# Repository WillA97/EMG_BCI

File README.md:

# EMG_BCI

## Introduction
This repository contains the documentation, hardware files, and software files for a simple electromyogram front end. The purpose is to create a simple interface to aquire the signals and also improve my hardware and software design skills. It's mostly for fun

## High level requirements

- Amplifier the signals from a 2 electrode from an EMG signal
- transfer the data from to a secondary device

## Hardware block diagram

```mermaid
graph TD
    A[EMG Electrodes<br>500 µV - 1 mV] --> B[Instrumentation Amplifier<br>Gain: 50<br>High Z, High CMRR]
    B --> C[High-Pass Filter<br>Cutoff: 10 Hz]
    C --> D[Gain Stage<br>Gain: 20<br>Total Gain: 1000]
    D --> E[Low-Pass Filter<br>Cutoff: 500 Hz]
    E --> F[Rectifier]
    E --> G[Offset Stage<br>Shift to 1.5V]
    G --> H[ADC 1<br>Un-rectified]
    F --> I[ADC 2<br>Rectified]

```
- The EMG signals will be around 500 uV - 1 mV. Will scale the signals with a gain of about 1000 to make the output swing around 0.5 - 1 V
- The first stage is the instrumentation amplifier. It has a very high impedence input, and large common mode rejection. It also has a gain stage built in, which is chosen as 50
- The second stage would be the high pass filter. Removed any high frequency signals and prevents aliasing when sampling occurs. The cutoff frequency is 10 Hz, which is the lower frequency of the muscle fibers
- The third stage is a gain stage. The gain is set to 20, putting the final gain at 1000.
- The fourth state is the low pass filter. The cutoff frequency was set to 500 Hz, which is the upper limit of the muscle fibers.
- The fifth stage is the rectifier stage.
- The sixth stage is the offset stage, which adds an offset to shift the 0 point of the signal to be 1.5V. This is because many microcontrollers use +3.3V and we want to avoid applying a negative voltage on the ADC
- The sevent stage is the ADC, which can record the EMG signals. To give some options about which signal can be used in the signal processing. I want to use one ADC for the un-rectified signal, and another for the rectified signal.

- There are a couple of options when using the signal for an EMG:
  
  - one option is to use the raw EMG data and do the signal processing on those values. After performing an FFT will get the frequency data from them
  - another option is to rectify the signal, this would give an positive average value for the signal
  - with the rectified signal, can take the RMS and filterd values of it to get the average value of the amount of exertion from the muscles
 
## Communication interface

- The communication interface will be used to transfer the digitized EMG signals to an external device. The ADC chosen (MCP 3202) uses an SPI interface.

## Test results 
Here are some of the results from testing the front end. The analog discovery module was used to insert a signal at the front of the instrumentation amplifier and the output at the different test points was recorded

### Instrumentation amplifier
The following table shows in the input and outputs for the instrumentation amplifier stage:

| Input | Offset | Output PK1 | Output PK2 | Out Offset | Diff | Gain | Offset Gain |
| :--- | :--- | :--- | :--- | :--- | :--- | :--- | :--- |
| 0.01 | 0.5 | 1.478 | 1.5204 | 1.4992 | 0.0424 | 4.24 | 1.8984 |
| 0.05 | 0.5 | 1.398 | 1.598 | 1.498 | 0.2 | 4 | 1.896 |
| 0.06 | 0.5 | 1.381 | 1.6175 | 1.49925 | 0.2365 | 3.94166667 | 1.8985 |
| 0.1 | 0.5 | 1.3 | 1.695 | 1.4975 | 0.395 | 3.95 | 1.895 |
| 0.15 | 0.5 | 1.202 | 1.796 | 1.499 | 0.594 | 3.96 | 1.898 |
| 0.05 | 0.1 | 0.621 | 0.819 | 0.72 | 0.198 | 3.96 | 1.7 |
| 0.05 | 0.2 | 0.814 | 1.01 | 0.912 | 0.196 | 3.92 | 1.81 |
| 0.05 | 0.4 | 1.207 | 1.402 | 1.3045 | 0.195 | 3.9 | 1.88625 |
| 0.05 | 0.6 | 1.596 | 1.792 | 1.694 | 0.196 | 3.92 | 1.90666667 |
| 0.05 | 0.7 | 1.789 | 1.985 | 1.887 | 0.196 | 3.92 | 1.91 |
| 0.05 | 0.8 | 1.984 | 2.181 | 2.0825 | 0.197 | 3.94 | 1.915625 |
| 0.05 | 0.9 | 2.181 | 2.376 | 2.2785 | 0.195 | 3.9 | 1.92055556 |
| 0.05 | 0 | 0.547 | 0.626 | 0.5865 | 0.079 | 1.58 | *Undefined (NaN)* |

couple of things to note:
- for some reason the gain of the amplifier is 4. From the datasheet since the gain pins is connected to HIGH it should be 50. Not sure why it isn't working as it should. Will have to do more investigation
- the offset did not work as I expected. It just cut off the zero point of the amplifier so when a negative value was put in, it was still cut off. I should have connected a negative supply to it in order to not lose the negative information or apply an offset to it using a summing amplifer. Since there is a high pass filter after it, the offset would likely removed anyways.

### TP2 - Output of the high pass filter and gain stage

The following table shows the data:

| Input | offset | output pk1 | output pk2 | out offset | diff | gain |
| :--- | :--- | :--- | :--- | :--- | :--- | :--- |
| 0.01 | 0.5 | -0.406 | 0.388 | -0.018 | 0.794 | 79.4 |
| 0.001 | 0.5 | -0.0375 | 0.0429 | 0.0054 | 0.0804 | 80.4 |
| 0.015 | 0.5 | -0.59 | 0.602 | 0.012 | 1.192 | 79.46667 |
| 0.02 | 0.5 | -0.782 | 0.798 | 0.016 | 1.58 | 79 |
| 0.03 | 0.5 | -1.118 | 1.1959 | 0.0159 | 2.3759 | 79.19667 |

### TP3 - Output of the low pass filter / The entire system

| Input | offset | output pk1 | output pk2 | out offset | diff | gain |
| :--- | :--- | :--- | :--- | :--- | :--- | :--- |
| 0.03 | 0.5 | -1.00E-02 | 5.64E-03 | -2.20E-03 | 1.57E-02 | 0.522333 |
| 0.03 | 0.5 | -6.79E-01 | 6.79E-01 | 0.00E+00 | 1.36E+00 | 45.26667 |
| 0.03 | 0.5 | -1.178 | 1.178 | 0.00E+00 | 2.36E+00 | 78.53333 |
| 0.03 | 0.5 | -1.178 | 1.178 | 0.00E+00 | 2.36E+00 | 78.53333 |
| 0.03 | 0.5 | -1.178 | 1.178 | 0.00E+00 | 2.36E+00 | 78.53333 |
| 0.03 | 0.5 | -1.1315 | 1.131 | -2.50E-04 | 2.26E+00 | 75.41667 |
| 0.03 | 0.5 | -1.014 | 1.014 | 0.00E+00 | 2.03E+00 | 67.6 |
| 0.03 | 0.5 | -8.62E-01 | 8.68E-01 | 3.00E-03 | 1.73E+00 | 57.66667 |
| 0.03 | 0.5 | -7.10E-01 | 7.04E-01 | -3.00E-03 | 1.41E+00 | 47.13333 |
| 0.03 | 0.5 | -5.64E-01 | 5.70E-01 | 3.00E-03 | 1.13E+00 | 37.8 |
| 0.03 | 0.5 | -4.70E-01 | 4.59E-01 | -5.50E-03 | 9.29E-01 | 30.96667 |
| 0.03 | 0.5 | -3.65E-01 | 3.71E-01 | 3.00E-03 | 7.36E-01 | 24.53333 |
| 0.03 | 0.5 | -3.12E-01 | 3.12E-01 | 0.00E+00 | 6.24E-01 | 20.8 |
| 0.03 | 0.5 | -2.01E-01 | 2.01E-01 | 0.00E+00 | 4.02E-01 | 13.4 |
| 0.03 | 0.5 | -1.45E-01 | 1.42E-01 | -1.50E-03 | 2.87E-01 | 9.566667 |
| 0.03 | 0

The graphs of the final table are:

The frequency response has the desired shape. The cutoff frequnecy is around 500 Hz. However, since the gain stage of the instrumentation amplifier was off for some reason, the final gain is off as well. This is annoying.

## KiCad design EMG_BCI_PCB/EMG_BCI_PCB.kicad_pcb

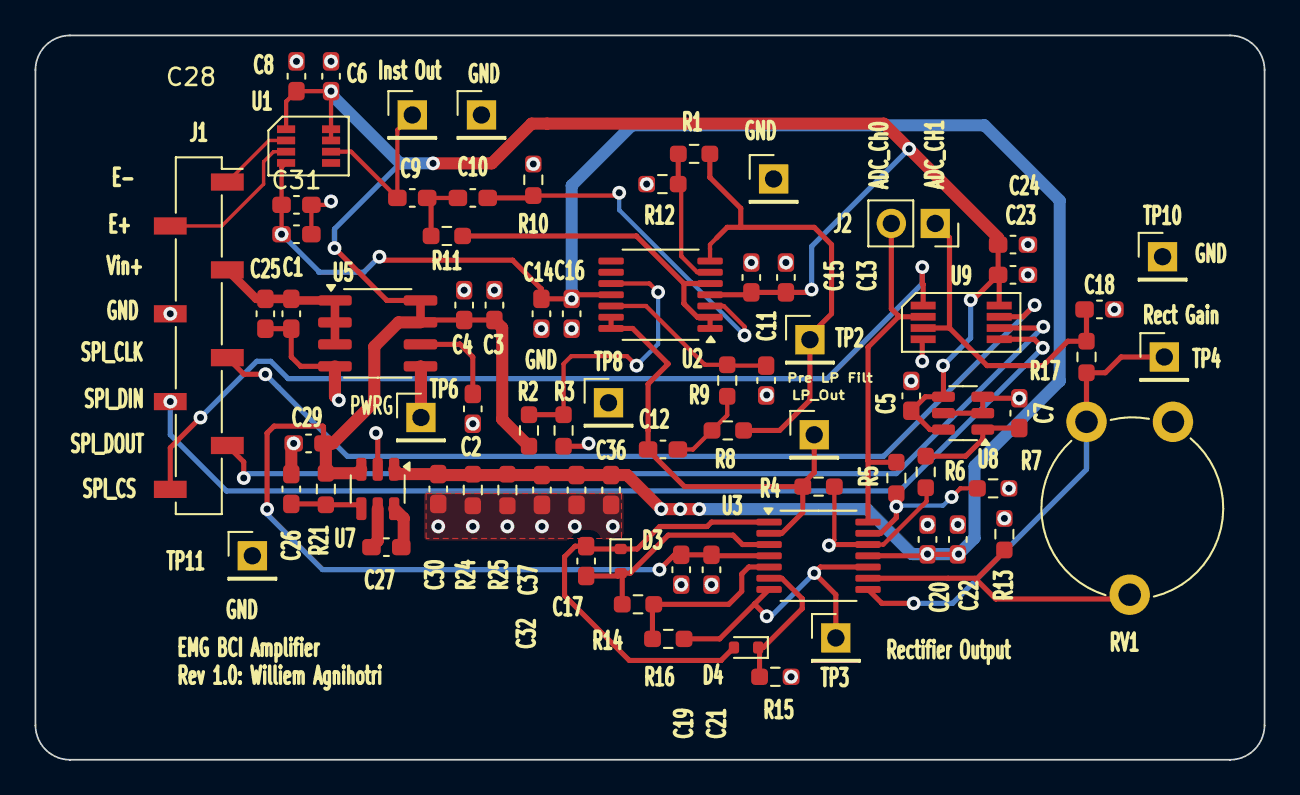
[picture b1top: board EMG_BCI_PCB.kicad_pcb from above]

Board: 4 copper layers, 71.1 x 41.9 mm, 77 parts (0 on the bottom side), 37 nets.

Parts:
C1, C3, C4, C25, C27: 1uF; C_0603_1608Metric_Pad1.08x0.95mm_HandSolder
C2: 1 nF; C_0603_1608Metric_Pad1.08x0.95mm_HandSolder
C5, C6, C7, C13, C14, C19, C20, C23, C28: 4.7uF; C_0603_1608Metric_Pad1.08x0.95mm_HandSolder
C8, C15, C16, C21, C22, C24, C31: 0.1uF; C_0603_1608Metric_Pad1.08x0.95mm_HandSolder
C9, C10: 1u; C_0603_1608Metric_Pad1.08x0.95mm_HandSolder
C11: 0.0047u; C_0603_1608Metric_Pad1.08x0.95mm_HandSolder
C12: 0.01u; C_0603_1608Metric_Pad1.08x0.95mm_HandSolder
C17: 47pF; C_0603_1608Metric_Pad1.08x0.95mm_HandSolder
C18, C26, C29, C30: 2.2uF; C_0603_1608Metric_Pad1.08x0.95mm_HandSolder
C32, C36, C37: 33u; C_0603_1608Metric_Pad1.08x0.95mm_HandSolder
D3, D4: 1N4148WT; D_SOD-523
J1: Conn_01x08_Pin; PinSocket_1x08_P2.54mm_Vertical_SMD_Pin1Right
J2: 2.54 mm header; PinSocket_1x02_P2.54mm_Vertical
R1: 190k; R_0603_1608Metric_Pad0.98x0.95mm_HandSolder
R2, R4, R5, R6, R7, R12: 10k; R_0603_1608Metric_Pad0.98x0.95mm_HandSolder
R3: 2k; R_0603_1608Metric_Pad0.98x0.95mm_HandSolder
R8: 56k; R_0603_1608Metric_Pad0.98x0.95mm_HandSolder
R9: 36k; R_0603_1608Metric_Pad0.98x0.95mm_HandSolder
R10: 22k; R_0603_1608Metric_Pad0.98x0.95mm_HandSolder
R11: 11k; R_0603_1608Metric_Pad0.98x0.95mm_HandSolder
R13, R14, R15, R16: 1K; R_0603_1608Metric_Pad0.98x0.95mm_HandSolder
R17: 72.5K; R_0603_1608Metric_Pad0.98x0.95mm_HandSolder
R21: 10K; R_0603_1608Metric_Pad0.98x0.95mm_HandSolder
R24, R25: 200; R_0603_1608Metric_Pad0.98x0.95mm_HandSolder
RV1: R_Potentiometer; Potentiometer_Piher_PT-10-V10_Vertical
TP1, TP2, TP3, TP4, TP5, TP6, TP7, TP8, TP9, TP10, TP11: TestPoint; PinHeader_1x01_P2.54mm_Vertical
U1: INA350CDS; SOT-23-THIN
U2, U3: ADA4807-4ARUZ; TSSOP-14_4.4x5mm_P0.65mm
U5: MCP1727-3302xSN; SOIC-8_3.9x4.9mm_P1.27mm
U7: LM2776; SOT-23-6
U8: MCP1501-18xCH; SOT-23-6
U9: MCP3202; 8-MSOP

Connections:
+3.3V: C3.1, C4.1, C5.2, C6.2, C8.2, C13.2, C15.2, C19.1, C21.1, C23.1, C24.1, C29.1, R2.1, R21.1, U1.1 (GS), U1.7 (Vs+), U1.8 (~SD), U2.4 (V+), U3.4 (V+), U5.7 (Sense), U5.8 (Vout), U7.3 (VIN), U8.4 (~SHDN), U8.6 (VDD), U9.8 (VDD/VREF)
-3V3: C14.2, C16.2, C20.1, C22.1, C28.1, C30.1, C31.1, C32.1, C36.1, C37.1, R24.1, R25.1, U1.4 (Vs-), U2.11 (V-), U3.11 (V-), U7.1 (VOUT)
/EMG_ADC/AdcCh0: J2.2, R5.1, U3.14, U9.2 (CH0)
/EMG_ADC/AdcCh1: C18.1, J2.1, R17.1, U9.3 (CH1)
/EMG_FrontEnd/Electrode+: J1.2, U1.3 (IN+)
/EMG_FrontEnd/Electrode-: J1.1, U1.2 (IN-)
/EMG_FrontEnd/LP_OUT: C12.2, TP1.1 (1_1), U2.13 (-), U2.14, U3.3 (+)
/Power/Vin+: C1.1, C25.1, J1.3, U5.1 (Vin), U5.2 (Vin), U5.3 (~SHDN)
/SPI_CLK: J1.5, U9.7 (CLK)
/SPI_CS: J1.8, U9.1 (~CS/SHDN)
/SPI_DIN: J1.6, U9.5 (DIN)
/SPI_DOUT: J1.7, U9.6 (DOUT)
Earth: C1.2, C2.2, C3.2, C4.2, C5.1, C6.1, C7.1, C8.1, C11.1, C13.1, C14.1, C15.1, C16.1, C18.2, C19.2, C20.2, C21.2, C22.2, C23.2, C24.2, C25.2, C26.2, C28.2, C29.2, C30.2, C31.2, C32.2, C36.2, C37.2, J1.4, R3.2, R7.2, R10.2, R12.2, R13.2, R15.1, R24.2, R25.2, TP7.1 (1_1), TP8.1 (1_1), TP9.1 (1_1), TP10.1 (1_1), TP11.1 (1_1), U5.4 (GND), U7.2 (GND), U8.2 (GND), U8.3 (GND), U8.5 (GND), U9.4 (VSS)
unnamed: C9.2, TP5.1 (1_1), U1.6
unnamed: C9.1, C10.2, R11.2
unnamed: C12.1, R8.1, R9.2
unnamed: C17.2, D3.2 (A), R14.2, U3.2 (-)
unnamed: C17.1, D3.1 (K), D4.2 (A), U3.1
unnamed: D4.1 (K), R15.2, U3.5 (+)
unnamed: R1.2, R8.2, TP2.1 (1_1), U2.7
unnamed: R17.2, RV1.1, TP4.1 (1_1), U3.8
unnamed: C10.1, R10.1, U2.3 (+)
unnamed: R11.1, U2.1, U2.2 (-), U2.5 (+)
unnamed: R1.1, R12.1, U2.6 (-)
unnamed: R2.2, R3.1
unnamed: C11.2, R9.1, U2.12 (+)
unnamed: R14.1, R16.2, U3.6 (-)
unnamed: R16.1, TP3.1 (1_1), U3.7, U3.10 (+)
unnamed: R13.1, RV1.2, U3.9 (-)
unnamed: R4.1, R6.1, U3.12 (+)
unnamed: R5.2, R7.1, U3.13 (-)
unnamed: C2.1, U5.6 (Cdelay)
unnamed: TP6.1 (1_1), U5.5 (PWRGD)
unnamed: C27.1, U7.5 (C1+)
unnamed: C27.2, U7.6 (C1-)
unnamed: C26.1, R21.2, U7.4 (EN)
unnamed: C7.2, R6.2, U8.1 (OUT)

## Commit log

2025-09-20 Add files from old front-end schematic
2025-09-20 Change to instrumnetation amplifier and filter circuitry
2025-09-21 More schematic changes
2025-09-21 Added power symbols for +/-3.3V
2025-09-21 Removed some warnings from the electrical rules
2025-09-21 Assigned footprints to components
2025-09-21 Removed inductors on power lines
2025-12-07 finally assigned the footprints to the schematic symbols
2025-12-07 Ran ERC again
2025-12-07 Imported footprints into layout
2025-12-08 Initial placement and routing
2025-12-31 Ordering the components
2025-12-31 Removes unecessary files
2026-04-26 PCB completed, and assembled
2026-04-26 Update communication interface description in README
2026-05-06 Adds initial LT spice simulation file
2026-05-06 Adds finished simulation of circuits
2026-05-18 Document test results for instrumentation amplifier
    Added test results and analysis for the instrumentation amplifier and filtering stages, including tables of input/output data and observations on performance.
2026-05-18 Add the negative voltage supply to the instrumentation amplifier
2026-05-18 corrected the active rectifier schematic
2026-05-20 Adjusts PCB and schematic with changes
